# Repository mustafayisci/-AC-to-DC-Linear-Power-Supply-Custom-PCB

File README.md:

# AC-to-DC Linear Power Supply & Custom PCB

A custom single-layer PCB power supply designed, simulated, fabricated, and tested for **EE 101** at Boğaziçi University. It converts a $10\,\text{V}$ AC ($50\,\text{Hz}$) input into a stabilized DC output using a full-wave bridge rectifier, capacitive filter, and Zener regulator.

---

## 🛠️ Design & Simulation
- **Architecture:** Full-wave bridge rectifier ($4\times$ 1N4001) $\rightarrow$ $2200\,\mu\text{F}$ filter ($\approx 80\,\text{mV}$ ripple) $\rightarrow$ Zener shunt regulator ($R_1 = 220\,\Omega$) $\rightarrow$ Status LED ($R_2 = 330\,\Omega$).
- **Verification:** Designed in **KiCad** and verified via transient analysis in **LTspice** before fabrication.

| Circuit Schematic (KiCad) | Transient Simulation (LTspice) |
| :---: | :---: |
|  |  |

---

## 🏭 PCB Fabrication & Lab Results
The single-layer FR4 board was fabricated in-house using **Positiv 20** photoresist coating, UV exposure, $0.7\%$ $\text{NaOH}$ developing, $\text{HCl} + \text{H}_2\text{O}_2$ chemical etching, drilling, and through-hole soldering.

| Parameter | Target / Computed | Measured (Lab) |
| :--- | :---: | :---: |
| **Input Voltage ($V_{\text{in}}$)** | $10\,\text{V}$ AC | $10.08\,\text{V}_{\text{rms}}$ |
| **Regulated Output ($V_{\text{out}}$)** | $4.70\,\text{V}$ DC | **$5.157\,\text{V}$ DC** |

> **Error Analysis:** The $0.457\,\text{V}$ deviation was traced to procuring a $5.0\,\text{V}$ Zener diode instead of $4.7\,\text{V}$. Relative to $5.0\,\text{V}$, the remaining $0.157\,\text{V}$ ($\approx 3.1\%$) error is within standard Zener manufacturing tolerance ($\pm 5\%$).

| Fabricated PCB | Lab Test Setup |
| :---: | :---: |
|  |  |

## 📂 Repository Structure

```text
├── docs/
│   └── EE101_Project_Report.pdf    # Full technical report
├── kicad/
│   ├── schematic.kicad_sch         # KiCad schematic file
│   └── layout.kicad_pcb            # KiCad PCB layout file
├── images/
│   ├── schematic.png
│   ├── pcb_layout.png
│   ├── ltspice_sim.png
│   ├── pcb_final.jpg
│   └── lab_test.jpg
└── README.md

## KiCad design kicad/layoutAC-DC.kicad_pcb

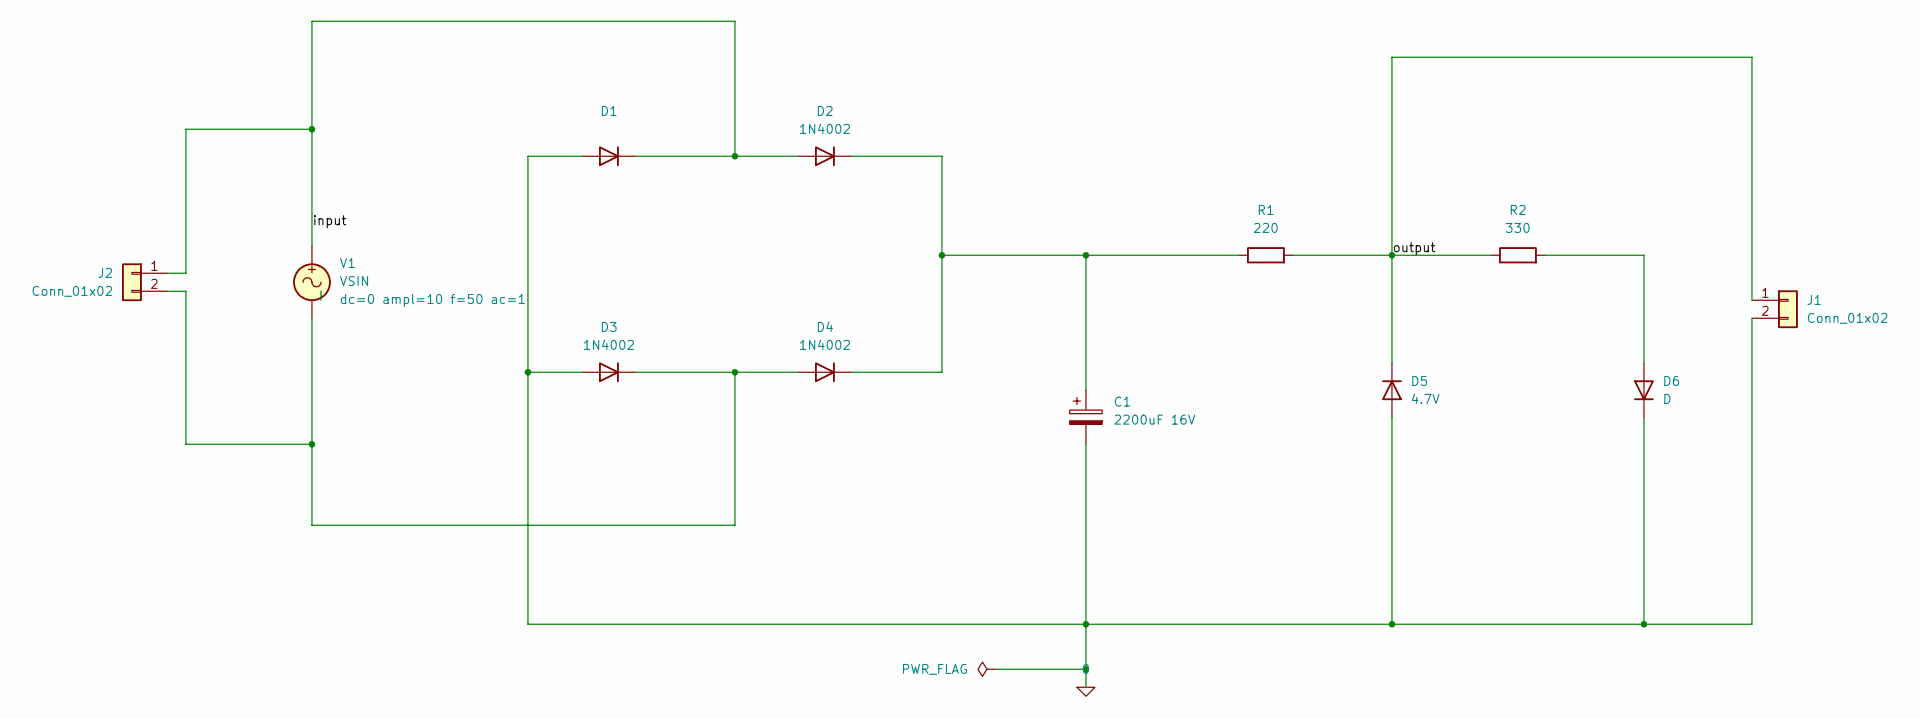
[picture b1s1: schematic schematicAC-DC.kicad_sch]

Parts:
C1: 2200uF 16V; CP_Radial_Tantal_D10.5mm_P5.00mm
D1, D2, D3, D4: 1N4002; D_DO-41_SOD81_P10.16mm_Horizontal
D5: 4.7V; D_DO-34_SOD68_P10.16mm_Horizontal
D6: D; LED_D5.0mm
J1, J2: Conn_01x02; TerminalBlock_MaiXu_MX126-5.0-02P_1x02_P5.00mm
R1: 220; R_Axial_DIN0207_L6.3mm_D2.5mm_P10.16mm_Horizontal
R2: 330; R_Axial_DIN0207_L6.3mm_D2.5mm_P10.16mm_Horizontal
V1: VSIN

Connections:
0: C1.2, D1.2 (A), D3.2 (A), D5.2 (A), D6.1 (K), J1.2
/<NO NET>: D1.1 (K), D2.2 (A), J2.1, V1.1
/output: D5.1 (K), J1.1, R1.2, R2.1
unnamed: C1.1, D2.1 (K), D4.1 (K), R1.1
unnamed: D3.1 (K), D4.2 (A), J2.2, V1.2
unnamed: D6.2 (A), R2.2

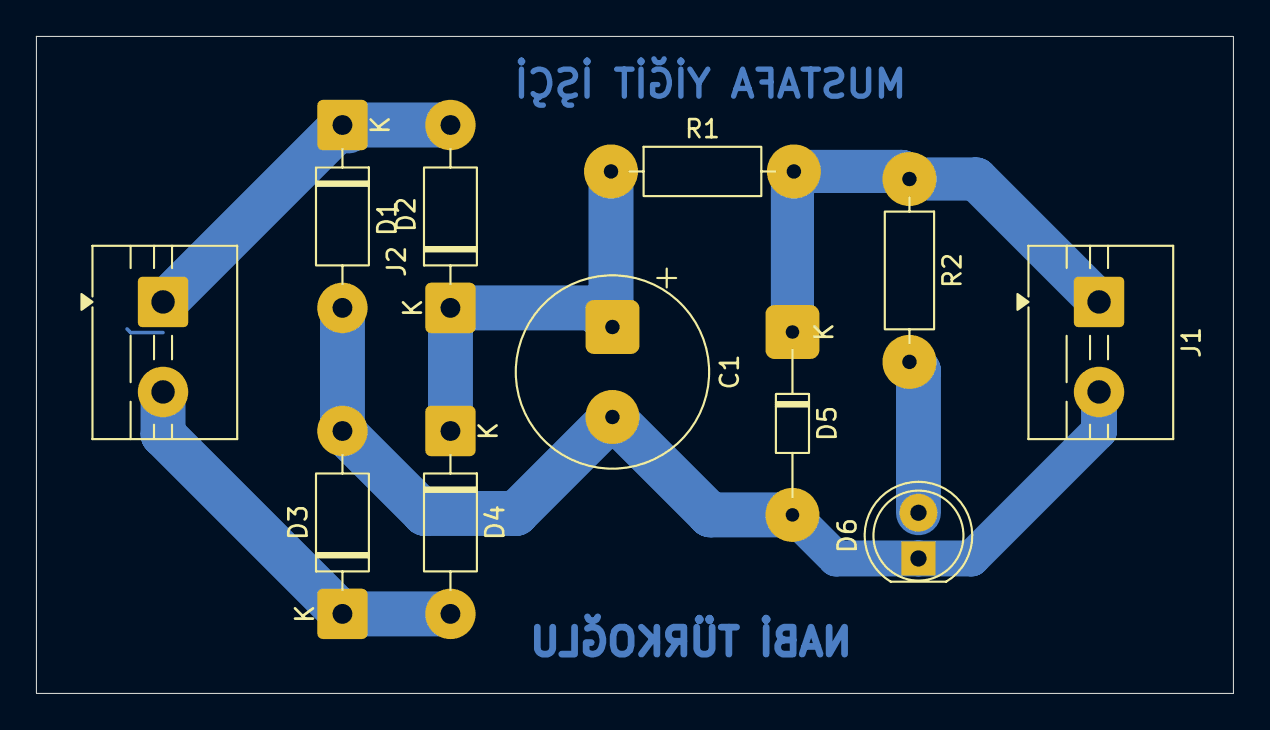
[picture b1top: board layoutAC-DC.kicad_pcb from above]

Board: 2 copper layers, 66.5 x 36.5 mm, 11 parts (0 on the bottom side), 6 nets.
